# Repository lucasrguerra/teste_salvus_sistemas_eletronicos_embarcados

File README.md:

# Teste Técnico para a vaga de Desenvolvedor de Sistemas Eletrônicos Embarcados na Salvus

## Descrição

Este repositório contém minhas respostas para o teste técnico para a vaga de Desenvolvedor de Sistemas Eletrônicos Embarcados na Salvus.

O arquivo [Teste Técnico](Teste_Técnico-Lucas_Rayan_Guerra_da_Silva.pdf) contém a descrição e as questões do teste técnico, assim como as minhas respostas para as questões 2, 3, 4 e 5.

A pasta [Projeto](Projeto) contém os arquivos do projeto do circuito de fonte de alimentação regulada para um microcontrolador de baixa potência que opera com 3.3V a partir de uma fonte de 12V e/ou uma bateria.

A pasta [Arquivos_de_Fabricação](Arquivos_de_Fabricação) contém os arquivos de fabricação do circuito de fonte de alimentação regulada.

O arquivo [Lista_de_Materiais_(BOM)](Lista_de_Materiais_(BOM).csv) contém a lista de materiais (BOM) do circuito de fonte de alimentação regulada.

O arquivo [Esquemático](Esquemático.pdf) contém o esquemático do circuito de fonte de alimentação regulada.

Por questões de tempo, não foi possível realizar a simulação do circuito de fonte de alimentação regulada, devido a utilização de componentes específicos que não são encontrados um equivalente para simulação com facilidade, não tive disposnibilidade o suficiente para catalogar todos eles. Porém, por utilizar um esquema de ligação muito semelhante ao utilizado nos módulos prontos comercializados com o chip TP4056, acredito que o circuito proposto funcione corretamente, garantindo a alternância entre a fonte de alimentação e bateria, bem como as proteções contra sobrecarga e descarga excessiva da bateria.

## Justificativa do uso dos componentes

### Conectores KF301-2P

Eles foram escolhidos por ser de fácil conexão e desconexão, além de serem baratos e fáceis de encontrar.

### Capacitor C1

Ele foi escolhido para filtrar o ruído da fonte de alimentação e garantir que a tensão de entrada do regulador de tensão seja o mais estável possível.

### LED D1

Esse LED na cor verde foi escolhido para indicar que a fonte de alimentação está conectada e funcionando.

### LED D2

Esse LED na cor vermelha foi escolhido para indicar que a bateria está sendo carregada.

### Regulador LM7805

Ele foi escolhido para regular a tensão de entrada de 12V para 5V, que é a tensão utilizada para carregar a bateria. Vale ressaltar que o regulador LM7805 aceita tensões de 7V até 20V, então o circuito pode ser alimentado com tensões de 7V até 20V.

### Regulador AP2112-3.3

Ele foi escolhido para regular a tensão de 5V vinda da fonte de alimentação, ou a tensão da bateria, para 3.3V, que é a tensão de alimentação do microcontrolador. A característica mais importante para essa aplicação é que ele é um LDO (Low Drop-Out), ou seja, ele pode ser alimentado com tensões muito próximas da tensão de saída, o que é o caso quando a bateria está sendo utilizada.

### TP4056

Ele foi escolhido para controlar a carga da bateria de lítio. Ele é um módulo de carga de bateria de lítio de 1A. Ele é muito utilizado em projetos de carregadores de bateria de lítio, por ser barato e fácil de encontrar.

### DW01A

Ele foi escolhido para proteger a bateria de lítio contra sobrecarga e descarga excessiva. Ele normalmente é utilizado em conjunto com o TP4056.

### MOSFET FS8205A

Ele foi escolhido para alternar entre a fonte de alimentação e a bateria. Ele é um MOSFET de canal duplo, e também costuma ser utilizado em conjunto com o TP4056.

### Extras

Também foram acionados 2 barramentos de 2.54mm com 2 pinos cada para facilitar a conexão da bateria e do MCU via Jumpers.

## Images

A pasta [Imagens](Imagens) contém as imagens do circuito de fonte de alimentação regulada mostradas abaixo.

Autor: Lucas Rayan Guerra da Silva

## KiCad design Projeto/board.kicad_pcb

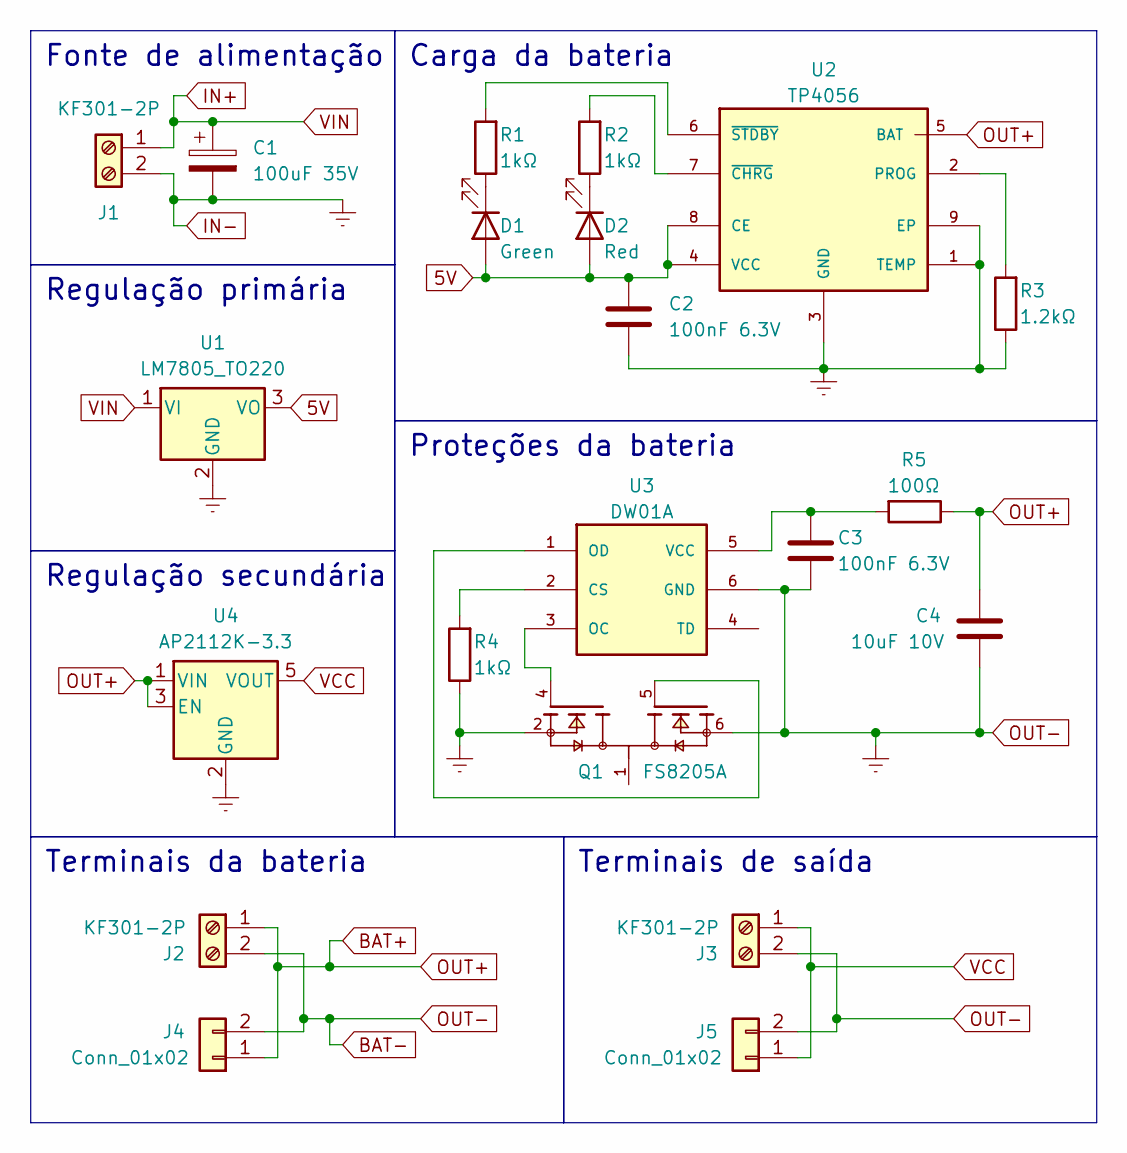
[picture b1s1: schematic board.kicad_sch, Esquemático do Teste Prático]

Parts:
C1: 100uF 35V; CP_Elec_6.3x7.7
C2, C3: 100nF 6.3V; C_0201_0603Metric
C4: 10uF 10V; C_0805_2012Metric
D1: Green; LED_0603_1608Metric
D2: Red; LED_0603_1608Metric
J1, J2, J3: KF301-2P; TerminalBlock_bornier-2_P5.08mm
J4, J5: Conn_01x02; PinHeader_1x02_P2.54mm_Vertical
Q1: FS8205A; SOP65P640X120-8N; PARTREV 1.7
R1, R2, R4: 1kΩ; R_0603_1608Metric
R3: 1.2kΩ; R_0603_1608Metric
R5: 100Ω; R_0603_1608Metric
U1: LM7805_TO220; TO-220-3_Horizontal_TabDown
U2: TP4056; SOP127P600X175-9N
U3: DW01A; SOT95P280X145-6N; PARTREV 1.8
U4: AP2112K-3.3; SOT-23-5

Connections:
5V: C2.1, D1.2 (A), D2.2 (A), U1.3 (VO), U2.4 (VCC), U2.8 (CE)
BAT+: C4.1, J2.1, J4.1, R5.1, U2.5 (BAT), U4.1 (VIN), U4.3 (EN)
BAT-: C1.2, C2.2, C3.2, C4.2, J1.2, J2.2, J3.2, J4.2, J5.2, Q1.2, Q1.6, R3.1, R4.1, U1.2 (GND), U2.1 (TEMP), U2.3 (GND), U2.9 (EP), U3.6 (GND), U4.2 (GND)
IN+: C1.1, J1.1, U1.1 (VI)
unnamed: D1.1 (K), R1.1
unnamed: D2.1 (K), R2.1
unnamed: R3.2, U2.2 (PROG)
unnamed: R2.2, U2.7 (~CHRG)
unnamed: R1.2, U2.6 (~STDBY)
unnamed: R4.2, U3.2 (CS)
unnamed: Q1.4, U3.3 (OC)
unnamed: Q1.5, U3.1 (OD)
unnamed: C3.1, R5.2, U3.5 (VCC)
VCC: J3.1, J5.1, U4.5 (VOUT)

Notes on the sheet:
Regulação primária
Proteções da bateria
Carga da bateria
Fonte de alimentação
Terminais da bateria
Regulação secundária
Terminais de saída

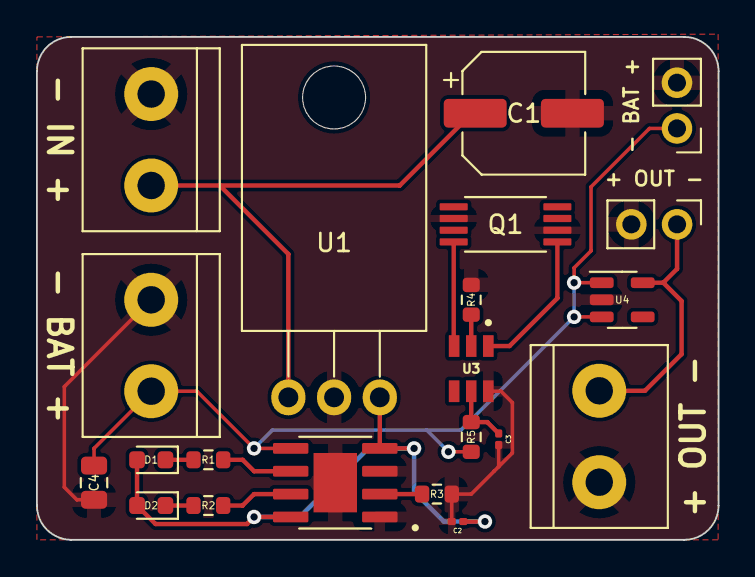
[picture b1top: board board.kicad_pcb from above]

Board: 2 copper layers, 37.9 x 27.9 mm, 21 parts (0 on the bottom side), 14 nets.

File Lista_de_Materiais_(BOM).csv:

Id,Designador,Footprint,Quantidade,Designação,Referência
1,D1,LED_0603_1608Metric,1,Green,LED Green 0603
2,"R2,R1,R4",R_0603_1608Metric,3,1kΩ,Resistor 1kΩ 0.1W 1% 0603
3,"J4,J5",PinHeader_1x02_P2.54mm_Vertical,2,Conn_01x02,Pin Header 1x02 2.54mm Vertical
4,C4,C_0805_2012Metric,1,10uF 10V,Capacitor 10uF 10V 2012
5,"J3,J1,J2",TerminalBlock_bornier-2_P5.08mm,3,KF301-2P,KF301-2P
6,U1,TO-220-3_Horizontal_TabDown,1,LM7805_TO220,LM7805_TO220
7,"C3,C2",C_0201_0603Metric,2,100nF 6.3V,Capacitor 100nF 6.3V 0603
8,U4,SOT-23-5,1,AP2112K-3.3,AP2112K-3.3
9,U2,SOP127P600X175-9N,1,TP4056,TP4056 SOP8
10,R3,R_0603_1608Metric,1,1.2kΩ,Resistor 1.2kΩ 0.1W 1% 0603
11,C1,CP_Elec_6.3x7.7,1,100uF 35V,Electrolytic capacitor 100uF 35V 6.3x7.7
12,Q1,SOP65P640X120-8N,1,FS8205A,FS8205A SOP8
13,D2,LED_0603_1608Metric,1,Red,LED Red 0603
14,R5,R_0603_1608Metric,1,100Ω,Resistor 100Ω 0.1W 1% 0603
15,U3,SOT95P280X145-6N,1,DW01A,DW01A SOT23

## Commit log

2024-07-16 Respostas
